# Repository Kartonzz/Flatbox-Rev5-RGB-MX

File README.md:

# Flatbox-Rev5-RGB-MX
A simple Flatbox Rev5 fork with support for MX-style switches and addressable RGBLED's 

Original design by jfedor: 

https://github.com/jfedor2/flatbox/tree/master/hardware-rev5

Switch/LED footprints from marbastlib and keyswitches pretty:

https://github.com/ebastler/marbastlib
https://github.com/daprice/keyswitches.pretty

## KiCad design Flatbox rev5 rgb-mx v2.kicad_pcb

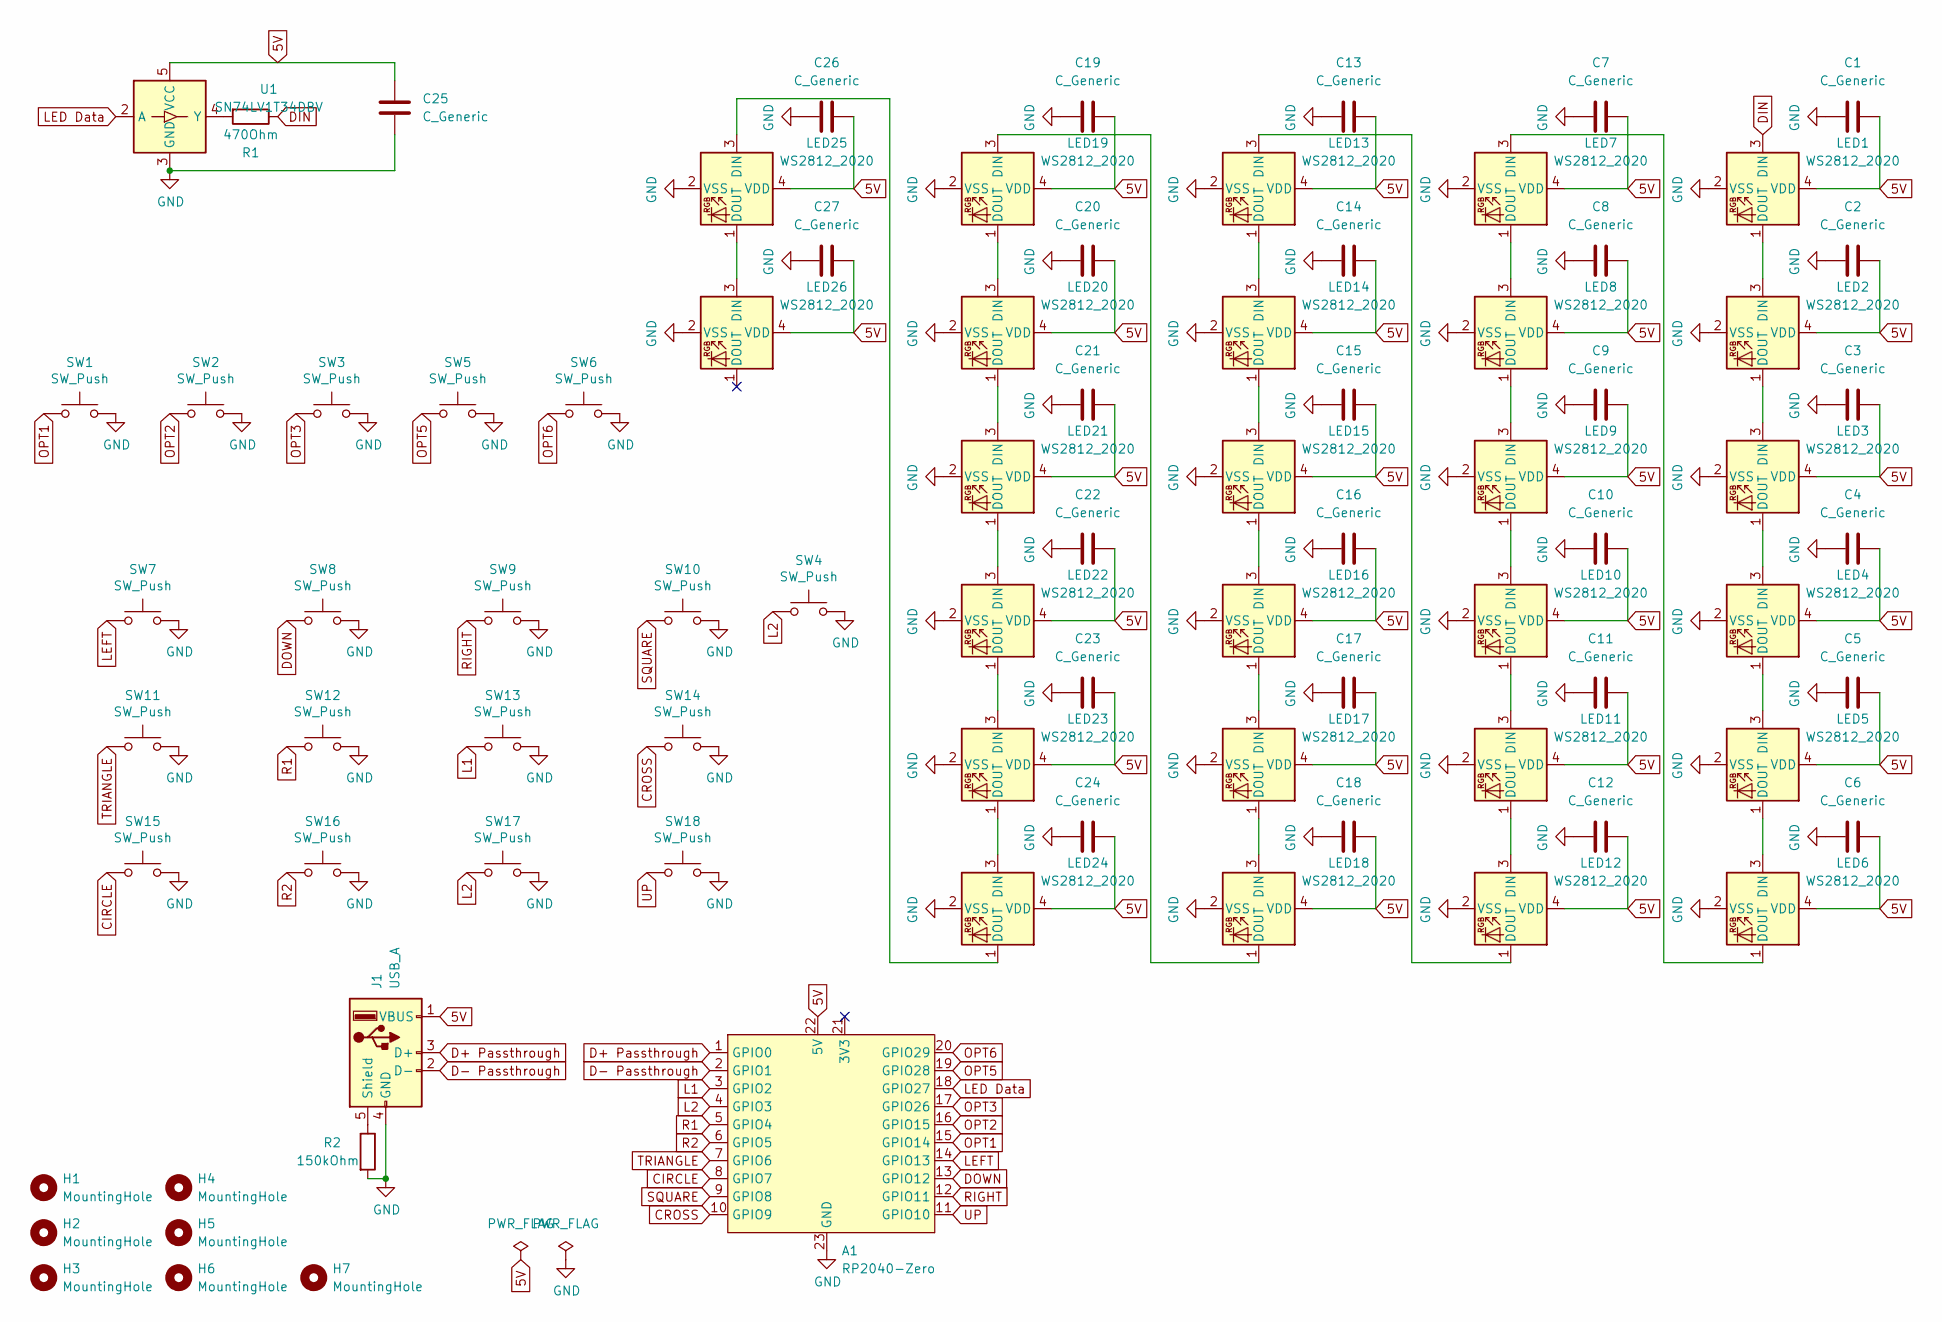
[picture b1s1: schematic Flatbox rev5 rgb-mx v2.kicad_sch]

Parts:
A1: RP2040-Zero
C1, C2, C3, C4, C5, C6, C7, C8, C9, C10, C11, C12, C13, C14, C15, C16, C17, C18, C19, C20, C21, C22, C23, C24, C25, C26, C27: C_Generic; C_0805_2012Metric
H1, H2, H3, H4, H5, H6, H7: MountingHole; MountingHole_6.4mm_M6
J1: USB_A; USB_A_CONNFLY_DS1095-WNR0
LED1, LED2, LED3, LED4, LED5, LED6, LED7, LED8, LED9, LED10, LED11, LED12, LED13, LED14, LED15, LED16, LED17, LED18, LED19, LED20, LED21, LED22, LED23, LED24, LED25, LED26: WS2812_2020; LED_WS2812_2020
R1: 470Ohm; R_0805_2012Metric
R2: 150kOhm; R_0805_2012Metric
SW1, SW2, SW3, SW5, SW6: SW_Push; SW_PUSH_6mm_H5mm
SW4, SW7, SW8, SW9, SW10, SW11, SW12, SW13, SW14, SW15, SW16, SW17, SW18: SW_Push; Kailh_socket_MX_optional
U1: SN74LV1T34DBV; SOT-23-5

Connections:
5V: A1.22 (5V), C1.1, C2.1, C3.1, C4.1, C5.1, C6.1, C7.1, C8.1, C9.1, C10.1, C11.1, C12.1, C13.1, C14.1, C15.1, C16.1, C17.1, C18.1, C19.1, C20.1, C21.1, C22.1, C23.1, C24.1, C25.1, C26.1, C27.1, J1.1 (VBUS), LED1.4 (VDD), LED2.4 (VDD), LED3.4 (VDD), LED4.4 (VDD), LED5.4 (VDD), LED6.4 (VDD), LED7.4 (VDD), LED8.4 (VDD), LED9.4 (VDD), LED10.4 (VDD), LED11.4 (VDD), LED12.4 (VDD), LED13.4 (VDD), LED14.4 (VDD), LED15.4 (VDD), LED16.4 (VDD), LED17.4 (VDD), LED18.4 (VDD), LED19.4 (VDD), LED20.4 (VDD), LED21.4 (VDD), LED22.4 (VDD), LED23.4 (VDD), LED24.4 (VDD), LED25.4 (VDD), LED26.4 (VDD), U1.5 (VCC)
CIRCLE: A1.8 (GPIO7), SW15.1
CROSS: A1.10 (GPIO9), SW14.1
D+ Passthrough: A1.1 (GPIO0), J1.3 (D+)
D- Passthrough: A1.2 (GPIO1), J1.2 (D-)
DIN: LED1.3 (DIN), R1.1
DOWN: A1.13 (GPIO12), SW8.1
GND: A1.23 (GND), C1.2, C2.2, C3.2, C4.2, C5.2, C6.2, C7.2, C8.2, C9.2, C10.2, C11.2, C12.2, C13.2, C14.2, C15.2, C16.2, C17.2, C18.2, C19.2, C20.2, C21.2, C22.2, C23.2, C24.2, C25.2, C26.2, C27.2, J1.4 (GND), LED1.2 (VSS), LED2.2 (VSS), LED3.2 (VSS), LED4.2 (VSS), LED5.2 (VSS), LED6.2 (VSS), LED7.2 (VSS), LED8.2 (VSS), LED9.2 (VSS), LED10.2 (VSS), LED11.2 (VSS), LED12.2 (VSS), LED13.2 (VSS), LED14.2 (VSS), LED15.2 (VSS), LED16.2 (VSS), LED17.2 (VSS), LED18.2 (VSS), LED19.2 (VSS), LED20.2 (VSS), LED21.2 (VSS), LED22.2 (VSS), LED23.2 (VSS), LED24.2 (VSS), LED25.2 (VSS), LED26.2 (VSS), R2.2, SW1.2, SW2.2, SW3.2, SW4.2, SW5.2, SW6.2, SW7.2, SW8.2, SW9.2, SW10.2, SW11.2, SW12.2, SW13.2, SW14.2, SW15.2, SW16.2, SW17.2, SW18.2, U1.3 (GND)
L1: A1.3 (GPIO2), SW13.1
L2: A1.4 (GPIO3), SW4.1, SW17.1
LED Data: A1.18 (GPIO27), U1.2 (A)
LEFT: A1.14 (GPIO13), SW7.1
unnamed: J1.5 (Shield), R2.1
unnamed: LED1.1 (DOUT), LED2.3 (DIN)
unnamed: LED2.1 (DOUT), LED3.3 (DIN)
unnamed: LED3.1 (DOUT), LED4.3 (DIN)
unnamed: LED4.1 (DOUT), LED5.3 (DIN)
unnamed: LED5.1 (DOUT), LED6.3 (DIN)
unnamed: LED6.1 (DOUT), LED7.3 (DIN)
unnamed: LED7.1 (DOUT), LED8.3 (DIN)
unnamed: LED8.1 (DOUT), LED9.3 (DIN)
unnamed: LED9.1 (DOUT), LED10.3 (DIN)
unnamed: LED10.1 (DOUT), LED11.3 (DIN)
unnamed: LED11.1 (DOUT), LED12.3 (DIN)
unnamed: LED12.1 (DOUT), LED13.3 (DIN)
unnamed: LED13.1 (DOUT), LED14.3 (DIN)
unnamed: LED14.1 (DOUT), LED15.3 (DIN)
unnamed: LED15.1 (DOUT), LED16.3 (DIN)
unnamed: LED16.1 (DOUT), LED17.3 (DIN)
unnamed: LED17.1 (DOUT), LED18.3 (DIN)
unnamed: LED18.1 (DOUT), LED19.3 (DIN)
unnamed: LED19.1 (DOUT), LED20.3 (DIN)
unnamed: LED20.1 (DOUT), LED21.3 (DIN)
unnamed: LED21.1 (DOUT), LED22.3 (DIN)
unnamed: LED22.1 (DOUT), LED23.3 (DIN)
unnamed: LED23.1 (DOUT), LED24.3 (DIN)
unnamed: LED24.1 (DOUT), LED25.3 (DIN)
unnamed: LED25.1 (DOUT), LED26.3 (DIN)
unnamed: R1.2, U1.4 (Y)
OPT1: A1.15 (GPIO14), SW1.1
OPT2: A1.16 (GPIO15), SW2.1
OPT3: A1.17 (GPIO26), SW3.1
OPT5: A1.19 (GPIO28), SW5.1
OPT6: A1.20 (GPIO29), SW6.1
R1: A1.5 (GPIO4), SW12.1
R2: A1.6 (GPIO5), SW16.1
RIGHT: A1.12 (GPIO11), SW9.1
SQUARE: A1.9 (GPIO8), SW10.1
TRIANGLE: A1.7 (GPIO6), SW11.1
UP: A1.11 (GPIO10), SW18.1

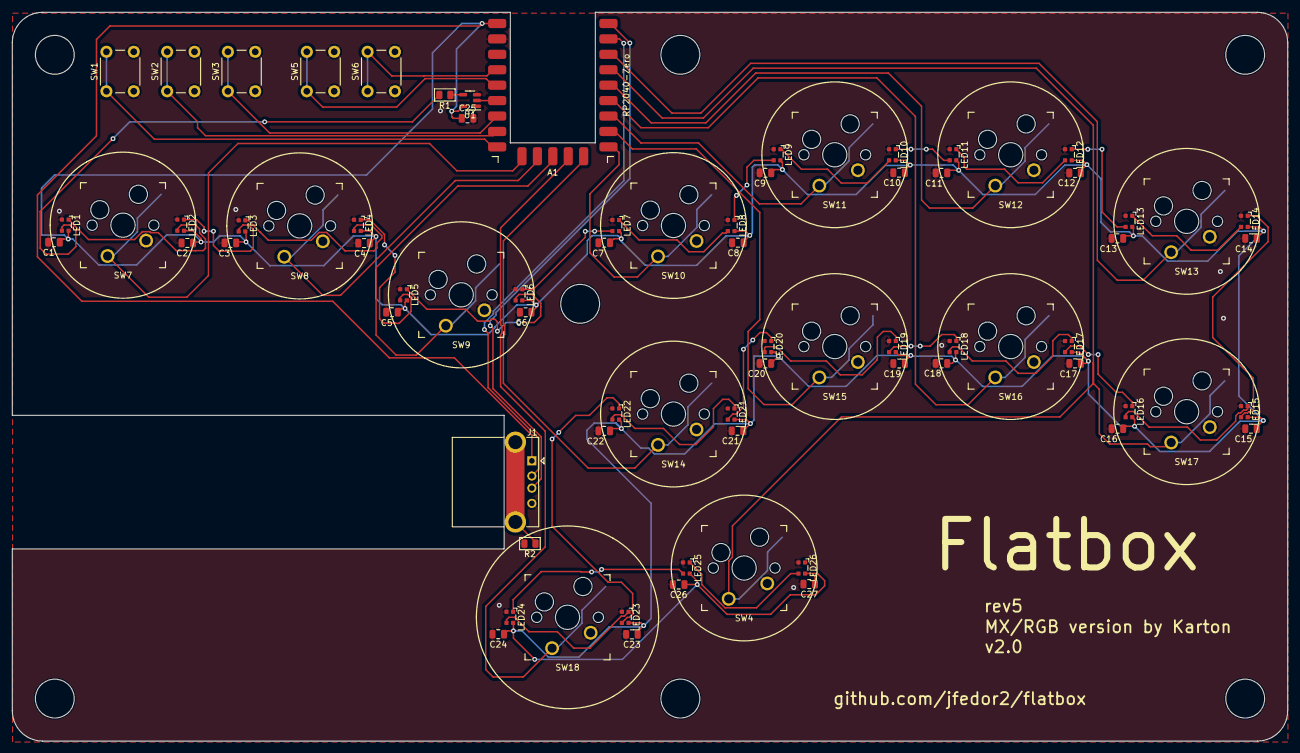
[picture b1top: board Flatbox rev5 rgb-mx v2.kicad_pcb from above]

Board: 2 copper layers, 210.0 x 120.0 mm, 83 parts (0 on the bottom side), 50 nets.

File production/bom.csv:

"Designator","Footprint","Quantity","Value","LCSC Part #"

"C1, C10, C11, C12, C13, C14, C15, C16, C17, C18, C19, C2, C20, C21, C22, C23, C24, C25, C26, C27, C3, C4, C5, C6, C7, C8, C9",805,27,"0.1uF","C138340"


"LED1, LED10, LED11, LED12, LED13, LED14, LED15, LED16, LED17, LED18, LED19, LED2, LED20, LED21, LED22, LED23, LED24, LED25, LED26, LED3, LED4, LED5, LED6, LED7, LED8, LED9","LED_WS2812_2020",26,"WS2812_2020","C965555"
"R1",805,1,"470Ohm","C204522"
"R2",805,1,"150kOhm","C114558"


"U1","SOT-23-5",1,"SN74LV1T34DBV","C100024"

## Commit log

2023-10-11 Add files via upload
    Production files for JLC.
2023-10-11 Add files via upload
    Source files for kicad, 2 kicad footprint folders for things changed from other libraries
